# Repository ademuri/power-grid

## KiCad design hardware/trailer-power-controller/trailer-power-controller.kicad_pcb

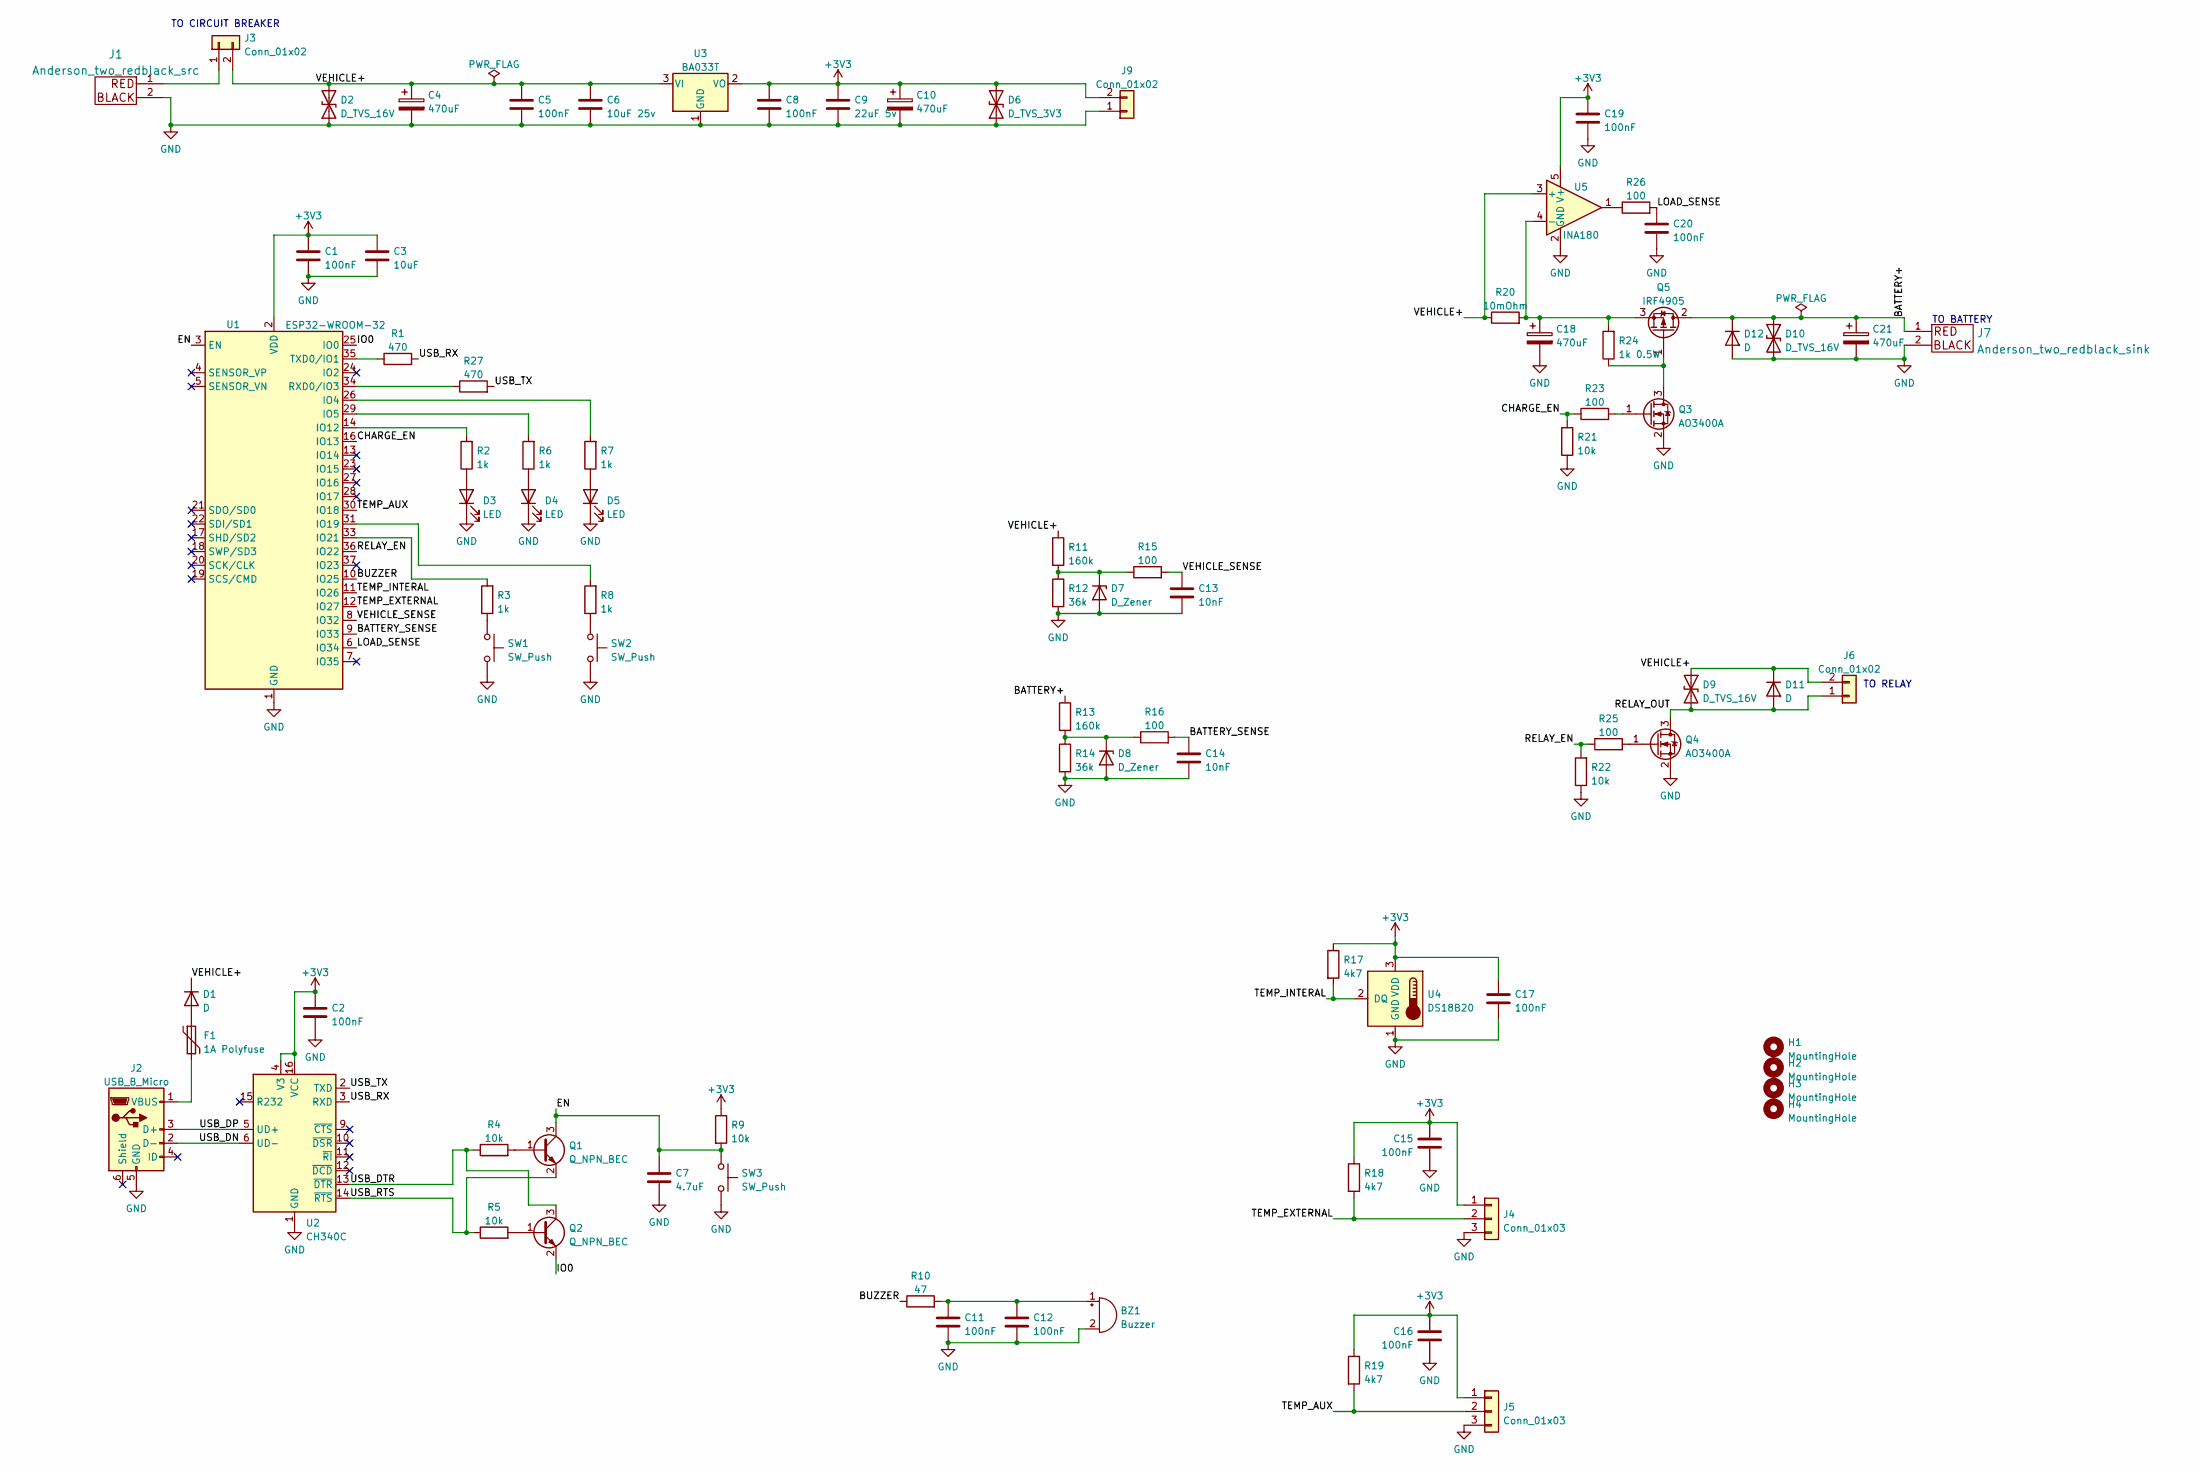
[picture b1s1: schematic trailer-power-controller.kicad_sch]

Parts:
BZ1: Buzzer; MURATA_PKM13EPYH4000-A0; MPN PKM13EPYH4000-A0
C1, C2, C5, C8, C11, C12, C15, C16, C17, C19, C20: 100nF; C_0402_1005Metric; LCSC C307331
C3: 10uF; C_0603_1608Metric; LCSC C96446
C4, C10, C18, C21: 470uF; CP_Radial_D10.0mm_P5.00mm
C6: 10uF 25v; C_0805_2012Metric; LCSC C440198
C7: 4.7uF; C_0402_1005Metric; LCSC C23733
C9: 22uF 5v; C_1206_3216Metric; LCSC C12891
C13, C14: 10nF; C_0402_1005Metric; LCSC C15195
D1, D11, D12: D; D_SOD-323; LCSC C191023
D2, D9, D10: D_TVS_16V; D_SMB; MPN SMBJ16CA
D3, D4, D5: LED; LED_0603_1608Metric; LCSC C2286
D6: D_TVS_3V3; D_SMB; MPN SMBJ4CA
D7, D8: D_Zener; D_MiniMELF; LCSC C8056
F1: 1A Polyfuse; Fuse_1206_3216Metric_Pad1.42x1.75mm_HandSolder; MPN PTS12066V100
H1, H2, H3, H4: MountingHole; MountingHole_3.2mm_M3
J1: Anderson_two_redblack_src; Anderson_1336G1_right_angle_bottom_two
J2: USB_B_Micro; FRAMATOME_10118194-0001LF_fixed_bridges; LCSC C132563
J3: Conn_01x02; SolderWire-12AWG_1x02; MPN W51-A152A1-15
J4, J5: Conn_01x03; MiniPV_69167-X03XXX_1x03_P2.54mm_Polarized_Vertical
J6: Conn_01x02; MiniPV_76384-X02XX_1x02_P2.54mm_Vertical
J7: Anderson_two_redblack_sink; Anderson_1336G1_right_angle_bottom_two
J9: Conn_01x02; PinHeader_1x02_P2.54mm_Vertical
Q1, Q2: Q_NPN_BEC; SOT-23; LCSC C2150
Q3, Q4: AO3400A; SOT-23; LCSC C20917
Q5: IRF4905; TO-220-3_Vertical; MPN IRF4905PBF
R1, R27: 470; R_0402_1005Metric; LCSC C25117
R2, R3, R6, R7, R8: 1k; R_0402_1005Metric; LCSC C11702
R4, R5, R9, R21, R22: 10k; R_0402_1005Metric; LCSC C25744
R10: 47; R_0402_1005Metric; LCSC C25118
R11, R13: 160k; R_0603_1608Metric; LCSC C22813
R12, R14: 36k; R_0603_1608Metric; LCSC C23147
R15, R16, R23, R25, R26: 100; R_0402_1005Metric; LCSC C25076
R17, R18, R19: 4k7; R_0402_1005Metric; LCSC C25900
R20: 10mOhm; R_2512_6332Metric_Pad1.40x3.35mm_HandSolder; MPN CRA2512-FZ-R010ELF
R24: 1k 0.5W; R_2512_6332Metric_Pad1.40x3.35mm_HandSolder; MPN CRM2512-JW-102ELF
SW1, SW2, SW3: SW_Push; SW_TACTILE_5.1MM_TS-1187A-C-D-B; LCSC C318884
U1: ESP32-WROOM-32; MPN ESP32-WROOM-32E-N4
U2: CH340C; SOIC-16_3.9x9.9mm_P1.27mm; LCSC C84681
U3: BA033T; TO-220-3_Vertical; MPN BA033T
U4: DS18B20; TO-92_Inline; MPN DS18B20
U5: INA180; SOT-23-5; MPN INA180A1IDBVR; LCSC C192764

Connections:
+3V3: C1.1, C2.2, C3.1, C8.1, C9.1, C10.1, C15.1, C16.1, C17.1, C19.1, D6.2 (A2), J4.1, J5.1, J9.2, R9.1, R17.1, R18.1, R19.1, U1.2 (VDD), U2.4 (V3), U2.16 (VCC), U3.2 (VO), U4.3 (VDD), U5.5 (V+)
/BATTERY+: C21.1, D10.1 (A1), D12.1 (K), J7.1, Q5.2 (D), R13.1
/BATTERY_SENSE: C14.1, R16.2, U1.9 (IO33)
/BUZZER: R10.1, U1.10 (IO25)
/CHARGE_EN: R21.2, R23.1, U1.16 (IO13)
/EN: C7.1, Q1.3 (C), R9.2, SW3.1, U1.3 (EN)
/IO0: Q2.2 (E), U1.25 (IO0)
/LOAD_SENSE: C20.1, R26.2, U1.6 (IO34)
/RELAY_EN: R22.2, R25.1, U1.36 (IO22)
/RELAY_OUT: D9.2 (A2), D11.2 (A), J6.1, Q4.3 (D)
/TEMP_AUX: J5.2, R19.2, U1.30 (IO18)
/TEMP_EXTERNAL: J4.2, R18.2, U1.12 (IO27)
/TEMP_INTERAL: R17.2, U1.11 (IO26), U4.2 (DQ)
/USB_DN: J2.2 (D-), U2.6 (UD-)
/USB_DP: J2.3 (D+), U2.5 (UD+)
/USB_DTR: Q2.3 (C), R4.1, U2.13 (~DTR)
/USB_RTS: Q1.2 (E), R5.1, U2.14 (~RTS)
/USB_RX: R1.2, U2.3 (RXD)
/USB_TX: R27.2, U2.2 (TXD)
/VEHICLE+: C4.1, C5.1, C6.1, D1.1 (K), D2.2 (A2), D9.1 (A1), D11.1 (K), J3.2, J6.2, R11.1, R20.1, U3.3 (VI), U5.3 (+)
/VEHICLE_SENSE: C13.1, R15.2, U1.8 (IO32)
GND: BZ1.2 (+), C1.2, C2.1, C3.2, C4.2, C5.2, C6.2, C7.2, C8.2, C9.2, C10.2, C11.2, C12.2, C13.2, C14.2, C15.2, C16.2, C17.2, C18.2, C19.2, C20.2, C21.2, D2.1 (A1), D3.1 (K), D4.1 (K), D5.1 (K), D6.1 (A1), D7.2 (A), D8.2 (A), D10.2 (A2), D12.2 (A), J1.2, J2.5 (GND), J4.3, J5.3, J7.2, J9.1, Q3.2 (S), Q4.2 (S), R12.2, R14.2, R21.1, R22.1, SW1.2, SW2.2, SW3.2, U1.1 (GND), U1.15 (GND), U1.38 (GND), U1.39 (GND), U2.1 (GND), U3.1 (GND), U4.1 (GND), U5.2 (GND)
unnamed: BZ1.1 (-), C11.1, C12.1, R10.2
unnamed: C18.1, Q5.3 (S), R20.2, R24.2, U5.4 (-)
unnamed: D1.2 (A), F1.1
unnamed: D3.2 (A), R2.1
unnamed: D4.2 (A), R6.1
unnamed: D5.2 (A), R7.1
unnamed: D7.1 (K), R11.2, R12.1, R15.1
unnamed: D8.1 (K), R13.2, R14.1, R16.1
unnamed: F1.2, J2.1 (VBUS)
unnamed: J1.1, J3.1
unnamed: Q1.1 (B), R4.2
unnamed: Q2.1 (B), R5.2
unnamed: Q3.1 (G), R23.2
unnamed: Q3.3 (D), Q5.1 (G), R24.1
unnamed: Q4.1 (G), R25.2
unnamed: R1.1, U1.35 (TXD0/IO1)
unnamed: R2.2, U1.14 (IO12)
unnamed: R3.1, SW1.1
unnamed: R3.2, U1.33 (IO21)
unnamed: R6.2, U1.29 (IO5)
unnamed: R7.2, U1.26 (IO4)
unnamed: R8.1, SW2.1
unnamed: R8.2, U1.31 (IO19)
unnamed: R26.1, U5.1
unnamed: R27.1, U1.34 (RXD0/IO3)

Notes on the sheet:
TO RELAY
TO BATTERY
TO CIRCUIT BREAKER

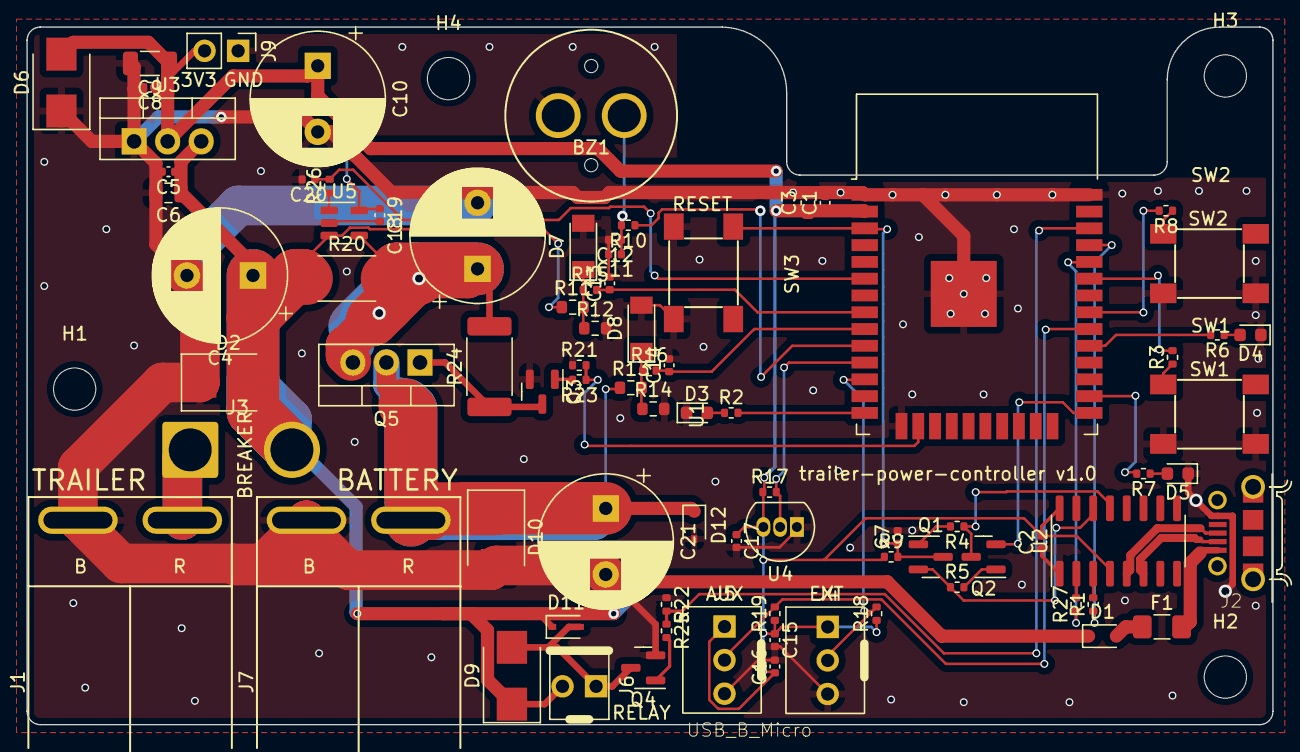
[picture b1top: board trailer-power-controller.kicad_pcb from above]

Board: 2 copper layers, 94.3 x 52.8 mm, 87 parts (0 on the bottom side), 47 nets.

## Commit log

2022-06-27 Add schematic and placement for trailer power controller
2022-06-28 Ignore backups
2022-06-28 trailer-power-controller hardware v1.0
2022-07-01 Pre-fab hardware v1.0 fixes
2022-07-21 Move PCB to subdir and create basic PIO project
2022-07-22 Add pin definitions
2022-07-22 Remove .pio and .vscode
2022-07-23 Add sense values to dashboard
2022-07-23 Fix voltage detection
2022-07-23 const -> constexpr
2022-07-23 Add basic power transfer logic
2022-07-23 Wait for battery to be low for some time before turning it off
2022-07-24 Check vehicle floating voltage
2022-07-24 Use AP mode instead of joining an extant network
2022-08-08 Add battery min detection
2022-08-15 Add 3d model for pcb
2022-08-16 Reset the inverter periodically
2022-08-16 Add temp and reduce dashboard digits
2022-08-16 Add internal temp, and blink alive LED
2022-08-16 Be more defensive in FormatFloat
2022-08-17 Add a tone on startup
2022-08-17 Fix cherry-pick
2022-08-18 Fix crashes, add OTA
2022-08-24 Also reset inverter at startup
2022-08-25 Simplify inverter logic
2022-08-25 Use SoftAP mode
